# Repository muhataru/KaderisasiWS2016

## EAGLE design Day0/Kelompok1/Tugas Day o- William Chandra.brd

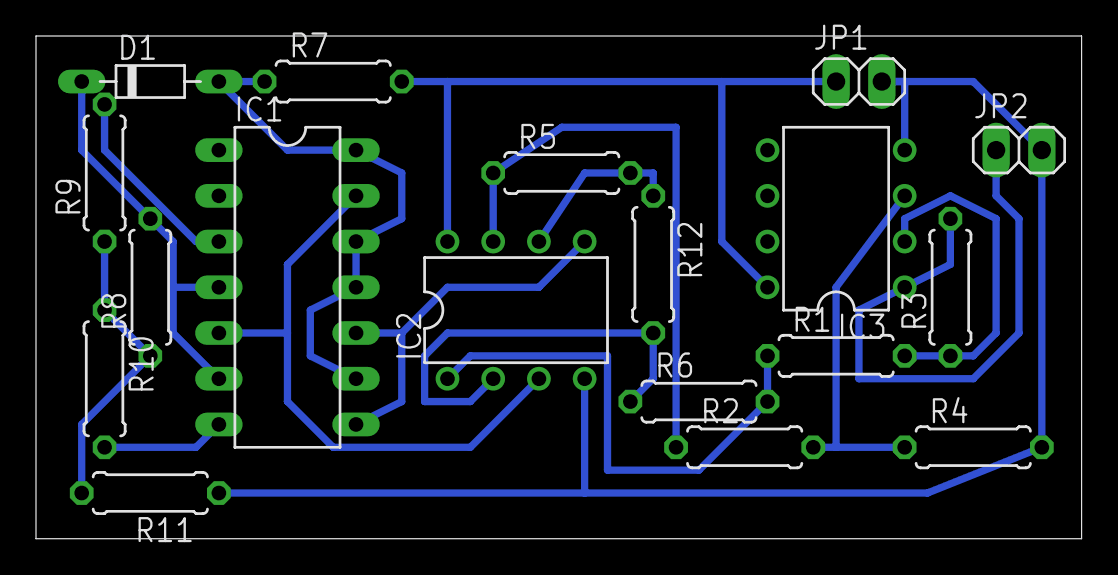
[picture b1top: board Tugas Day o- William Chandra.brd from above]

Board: 2 copper layers, 58.1 x 27.9 mm, 18 parts (0 on the bottom side), 16 nets.

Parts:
D1: D-7.5
IC1: DIL14
IC2, IC3: LM358N; DIL08
JP1, JP2: 1X02
R1, R2, R3, R4, R5, R6, R9: 100k; 0207/7
R7, R11: 60k; 0207/7
R8: 12k; 0207/7
R10: 200k; 0207/7
R12: 1k; 0207/7

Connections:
GND: IC2.4, IC3.4, JP1.2, JP2.2, R4.2, R11.1
unnamed: IC3.3, R2.2, R4.1
unnamed: IC3.2, R1.2, R3.1
unnamed: IC2.1, R1.1, R6.2
unnamed: IC2.2, R6.1, R12.2
unnamed: IC2.6, R5.2, R12.1
unnamed: IC2.7, R2.1, R5.1
unnamed: R8.1, R9.1, R10.1, R11.2
unnamed: D1.C, IC1.4, IC1.6, R8.2
unnamed: IC1.7, R10.2
unnamed: IC1.3, R9.2
unnamed: D1.A, IC1.9, IC1.11, IC1.12, IC1.14, R7.1
unnamed: IC1.5, IC1.13, IC2.3
unnamed: IC1.8, IC1.10, IC2.5
VCC: IC2.8, IC3.8, JP1.1, R7.2
VOUT: IC3.1, JP2.1, R3.2

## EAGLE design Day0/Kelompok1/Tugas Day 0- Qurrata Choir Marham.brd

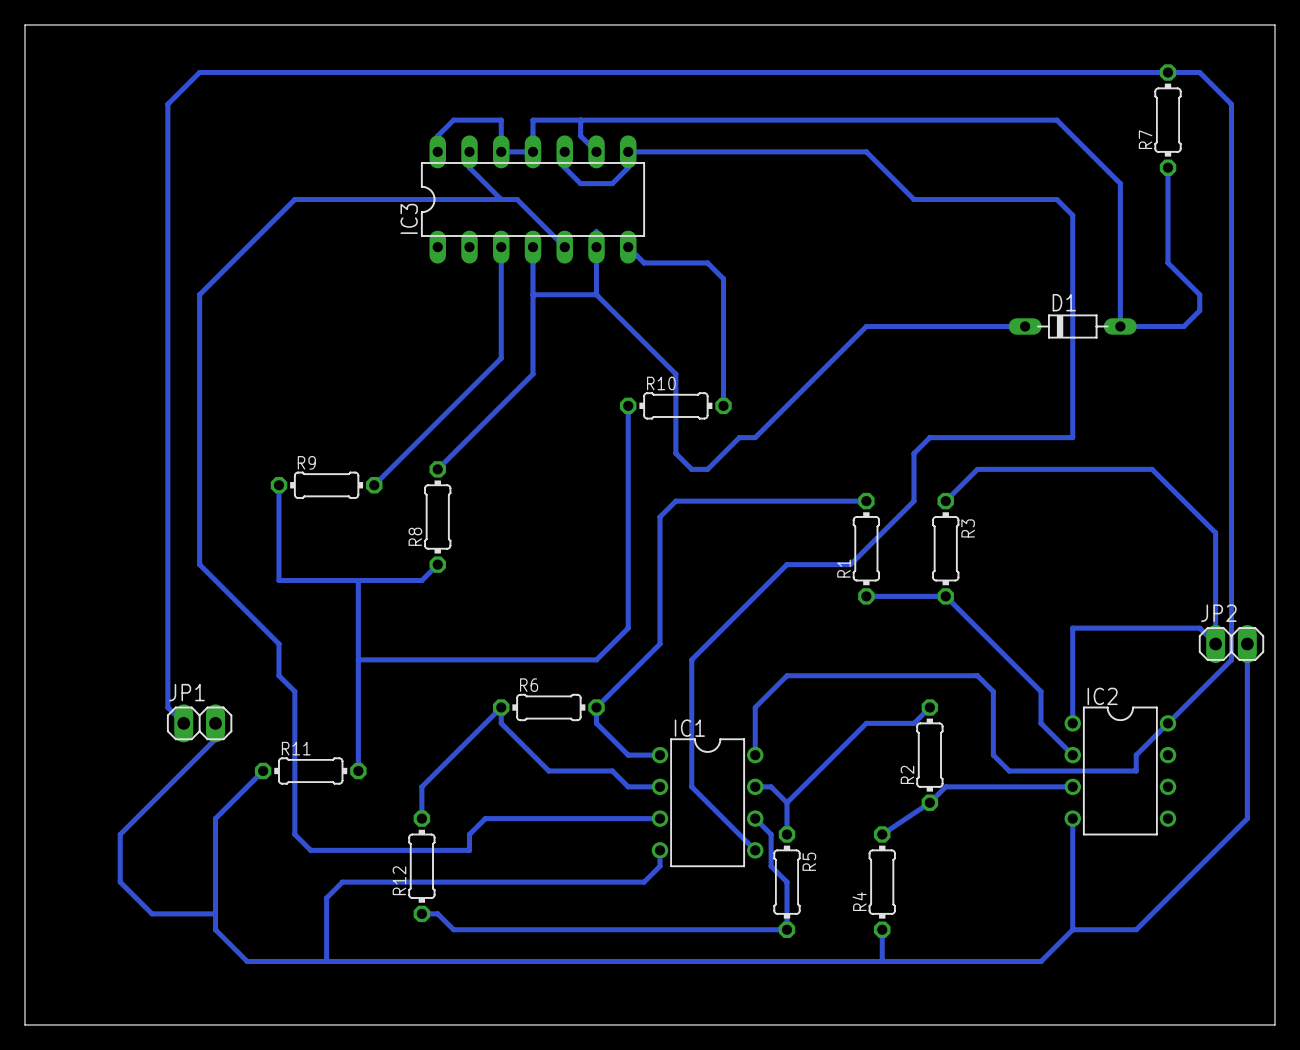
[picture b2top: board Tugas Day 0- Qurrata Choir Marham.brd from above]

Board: 2 copper layers, 100.0 x 80.0 mm, 18 parts (0 on the bottom side), 16 nets.

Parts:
D1: D-7.5
IC1, IC2: LM358N; DIL08
IC3: DIL14
JP1, JP2: 1X02
R1, R2, R3, R4, R5, R6, R9: 100k; 0204/7
R7, R11: 60k; 0204/7
R8: 12k; 0204/7
R10: 200k; 0204/7
R12: 1k; 0204/7

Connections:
GND: IC1.4, IC2.4, JP1.2, JP2.2, R4.1, R11.1
unnamed: D1.A, IC3.9, IC3.11, IC3.12, IC3.14, R7.1
unnamed: D1.C, IC3.4, IC3.6, R8.2
unnamed: IC3.3, R9.2
unnamed: IC3.7, R10.2
unnamed: R8.1, R9.1, R10.1, R11.2
unnamed: IC1.3, IC3.5, IC3.13
unnamed: IC1.5, IC3.8, IC3.10
unnamed: IC1.1, R1.2, R6.2
unnamed: IC1.6, R5.2, R12.1
unnamed: IC1.7, R2.2, R5.1
unnamed: IC1.2, R6.1, R12.2
unnamed: IC2.2, R1.1, R3.2
unnamed: IC2.3, R2.1, R4.2
VCC: IC1.8, IC2.8, JP1.1, R7.2
VOUT: IC2.1, JP2.1, R3.1

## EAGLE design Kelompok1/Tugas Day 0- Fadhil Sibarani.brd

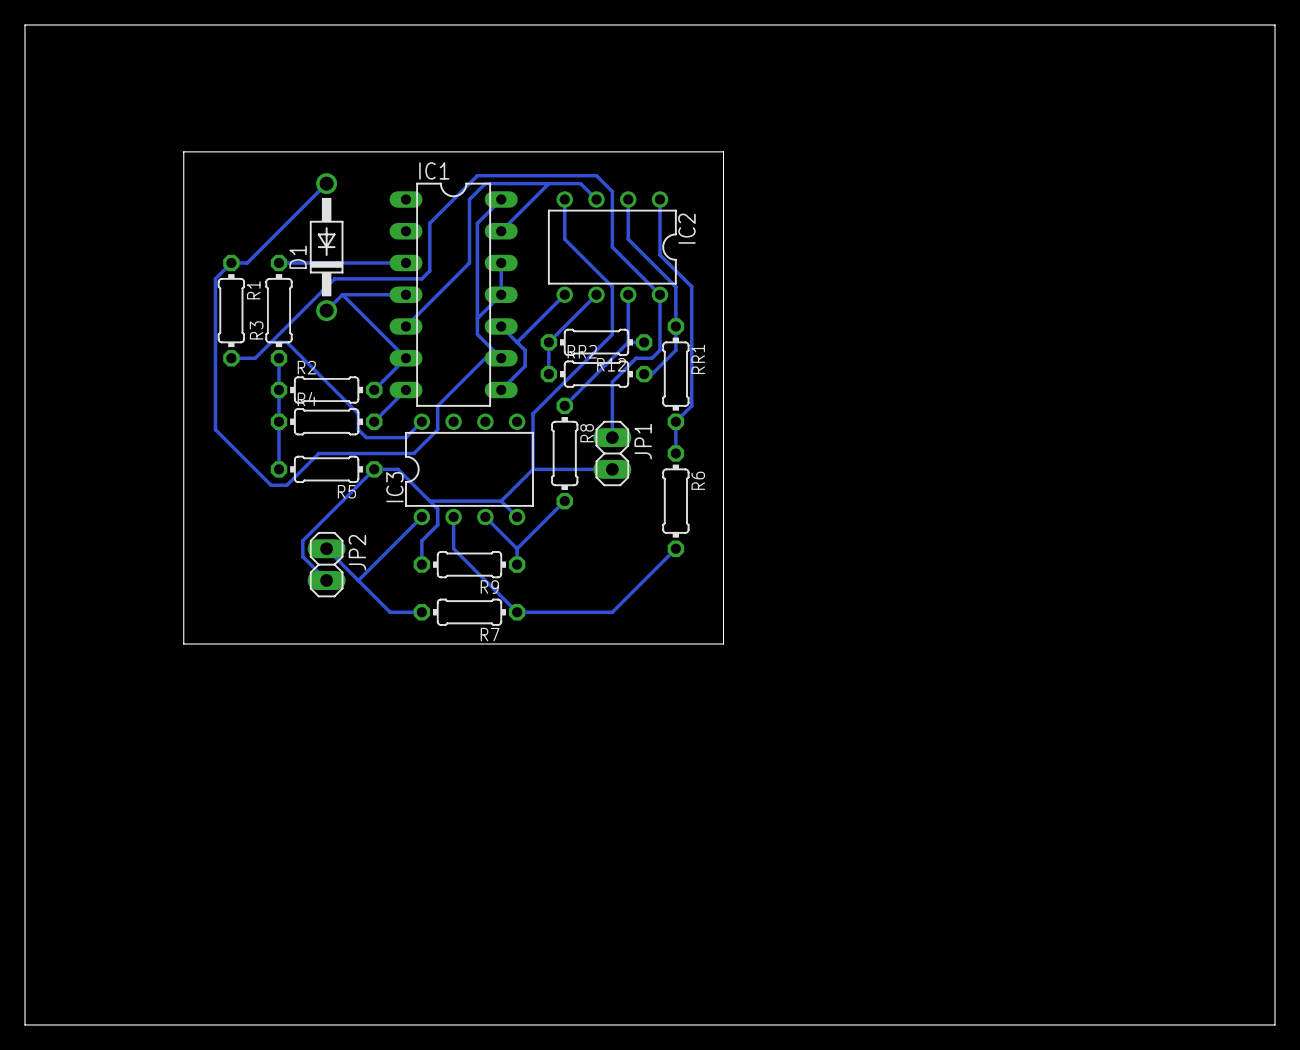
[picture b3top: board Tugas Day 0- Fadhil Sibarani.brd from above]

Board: 2 copper layers, 100.0 x 80.0 mm, 18 parts (0 on the bottom side), 16 nets.

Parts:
D1: 1N4004; DO41-10
IC1: CA3046; DIL14
IC2, IC3: LM358N; DIL08
JP1: MALE_HEADER 1; 1X02
JP2: MALE_HEADER 2; 1X02
R1, R5: 60K; 0204/7
R2: 12K; 0204/7
R3, R6, R7, R8, R9, R12: 100K; 0204/7
R4: 200K; 0204/7
RR1: 100K; 0204/7
RR2: 1K; 0204/7

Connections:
GND: IC2.4, IC3.4, JP1.2, JP2.2, R5.1, R9.2
unnamed: IC2.6, R12.2, RR2.1
unnamed: IC2.7, R8.1, R12.1
unnamed: R2.1, R3.1, R4.1, R5.2
unnamed: D1.C, IC1.4, IC1.6, R2.2
unnamed: IC1.3, R3.2
unnamed: IC1.7, R4.2
unnamed: IC1.8, IC1.10, IC2.5
unnamed: IC2.2, RR1.1, RR2.2
unnamed: IC1.5, IC1.13, IC2.3
unnamed: IC2.1, R6.1, RR1.2
unnamed: IC3.3, R8.2, R9.1
unnamed: IC3.2, R6.2, R7.1
unnamed: D1.A, IC1.9, IC1.11, IC1.12, IC1.14, R1.1
VCC: IC2.8, IC3.8, JP1.1, R1.2
VOUT: IC3.1, JP2.1, R7.2

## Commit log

2016-09-24 Create Kelompok1
